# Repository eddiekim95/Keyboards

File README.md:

# Keyboards
Various keyboards designed through KiCad.

**Dualies_Split_Keyboard:**
- A split keyboard design featuring low profile switches and rotary encoders.

**Numpad:**
 - A 5x4 numpad KiCad project. Originally handwired.

**Split_Ortho:**
  - A standard split ortholinear. Used as a practice environment for learning KiCad.

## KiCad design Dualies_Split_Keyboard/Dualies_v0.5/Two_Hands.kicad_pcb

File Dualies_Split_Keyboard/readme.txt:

#Dualies_Split_Keyboard
A split keyboard with KiCad design and gerber files

**v0.5 -**

Initial version of a split ortholinear keyboard. Loosely modeled after the Sofle and the Lily58.
Designed around the Kailh Choc low profile switch.
Designed so each PCB can be flipped for each respective side.

Components:
  - [60] Kailh Choc low profile switches (30 for each side)
  - [62] 1N4148W Diodes (31x2)
  - [60] YS-SK6812MINI-E Addressable RGB LED (30x2)
  - [2] Pro Micro Microcontroller (1x2)
  - [2] SSD1306 OLED Display Module (1x2)
  - [2] EC11 Digital Encoder (1x2)
  - [2] TRRS Jack (1x2)
  - [2] 2.54mm pitch, 15.24mm chip socket (1x2)
  - [2] 3.5mm TRRS Cable (1x2)
 
**v1.0 -**

Optimized wire pathing and switch spacing. 
Better standoff placements. 
Added switch plate and bottom plate files.
Images of the files can be seen in the Pictures folder.

Components: 
  - (same as v0.5)

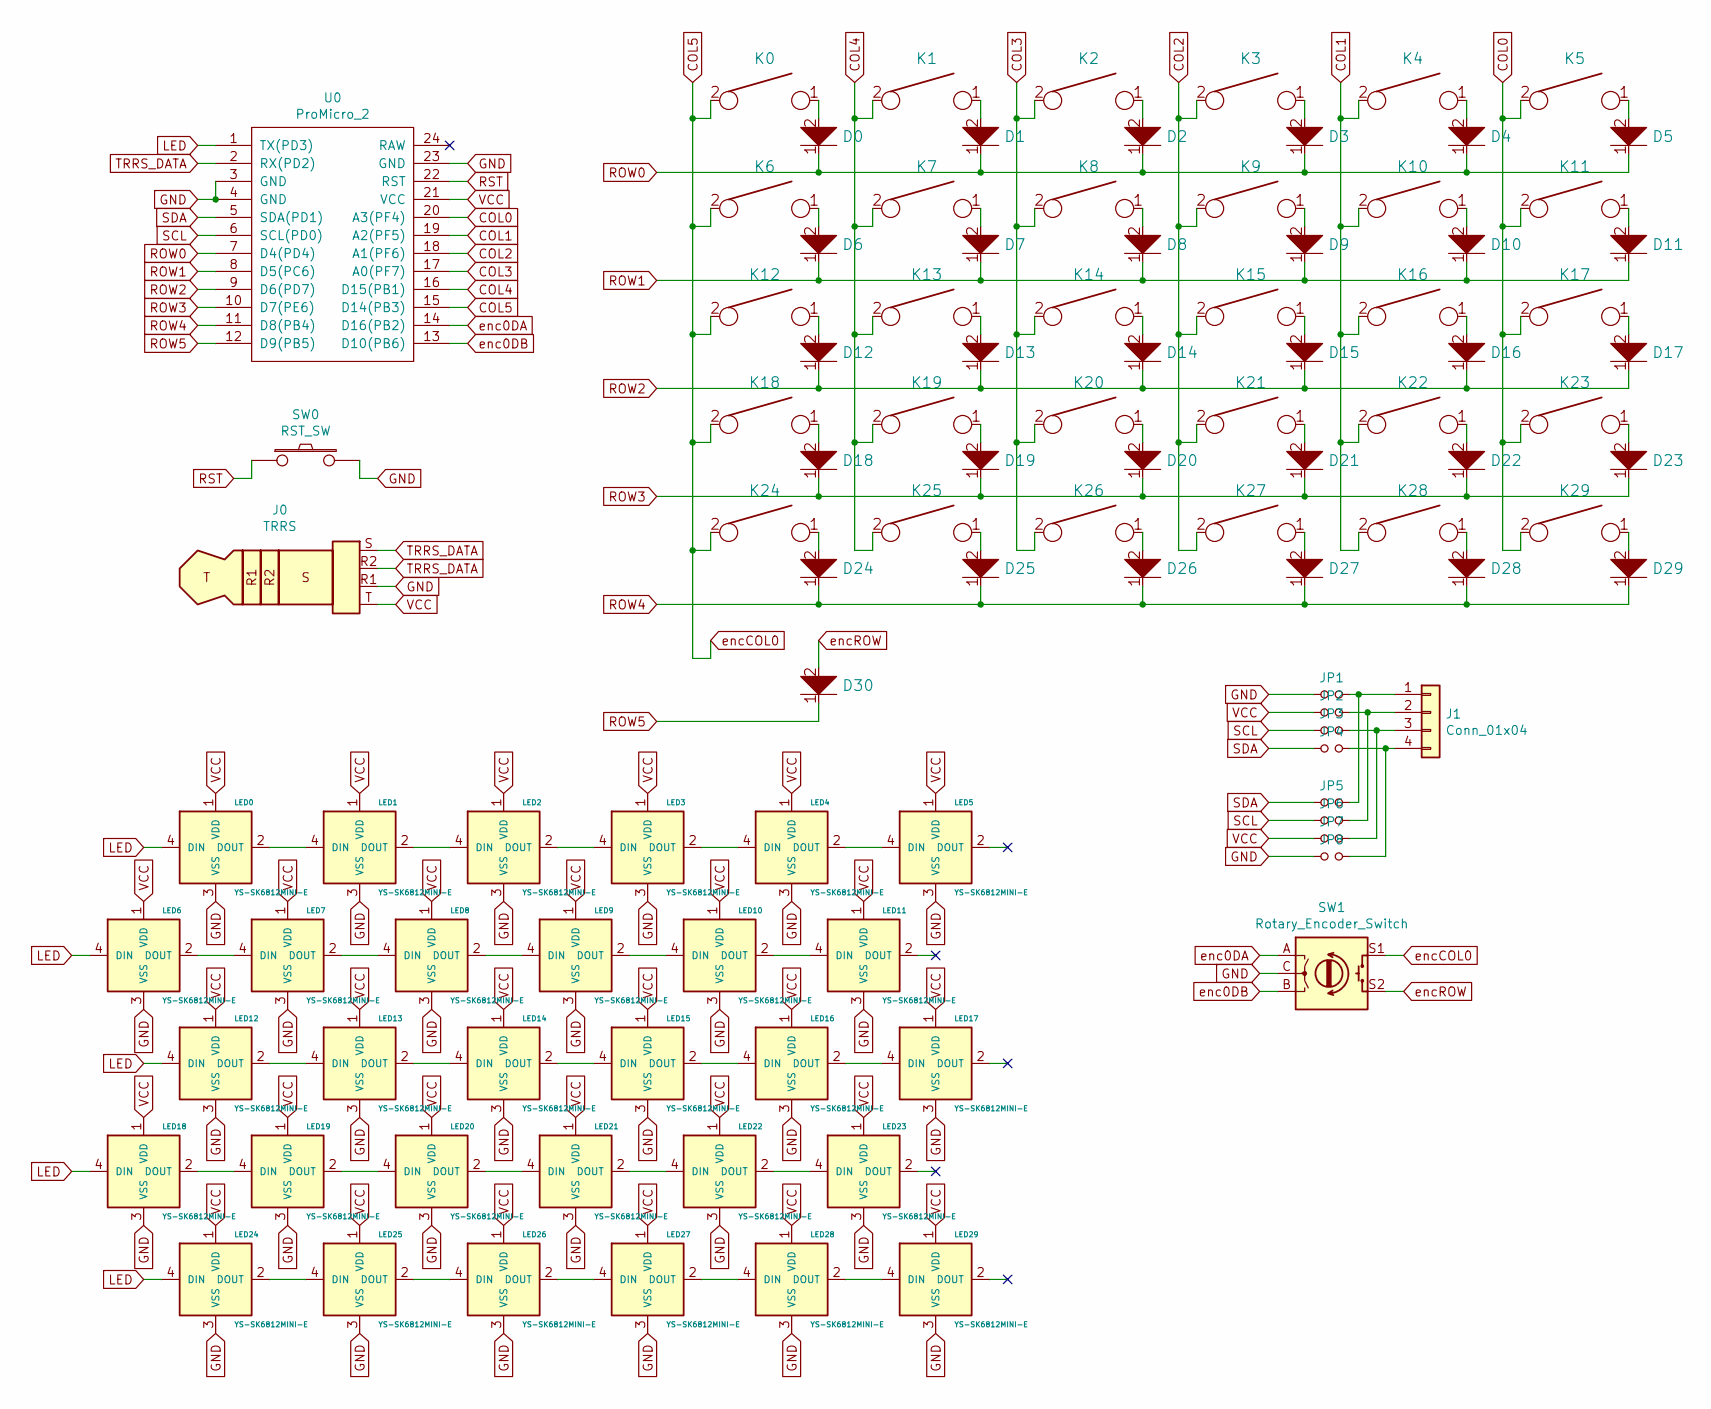
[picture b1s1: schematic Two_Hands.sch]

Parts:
D0, D1, D2, D3, D4, D5, D6, D7, D8, D9, D10, D11, D12, D13, D14, D15, D16, D17, D18, D19, D20, D21, D22, D23, D24, D25, D26, D27, D28, D29, D30: D; D_SOD123_axial_double
J0: TRRS; Jack_3.5mm_PJ320D_double
J1: Conn_01x04; PinHeader_1x04_P2.54mm_Vertical
JP1, JP2, JP3, JP4, JP5, JP6, JP7, JP8: Jumper_NO_Small; SolderJumper-2_P1.3mm_Open_Pad1.0x1.5mm
K0, K1, K2, K3, K4, K5, K6, K7, K8, K9, K10, K11, K12, K13, K14, K15, K16, K17, K18, K19, K20, K21, K22, K23, K24, K25, K26, K27, K28, K29: KEYSW; Kailh_Choc_100_Reversible
LED0, LED1, LED2, LED3, LED4, LED5, LED6, LED7, LED8, LED9, LED10, LED11, LED12, LED13, LED14, LED15, LED16, LED17, LED18, LED19, LED20, LED21, LED22, LED23, LED24, LED25, LED26, LED27, LED28, LED29: YS-SK6812MINI-E; YS-SK6812MINI-E_double
SW0: RST_SW; SW_PUSH_6mm
SW1: Rotary_Encoder_Switch; RotaryEncoder_Alps_EC12E-Switch_Vertical_H20mm
U0: ProMicro_2; ProMicro_double

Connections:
COL0: K5.2, K11.2, K17.2, K23.2, K29.2, U0.20 (A3(PF4))
COL1: K4.2, K10.2, K16.2, K22.2, K28.2, U0.19 (A2(PF5))
COL2: K3.2, K9.2, K15.2, K21.2, K27.2, U0.18 (A1(PF6))
COL3: K2.2, K8.2, K14.2, K20.2, K26.2, U0.17 (A0(PF7))
COL4: K1.2, K7.2, K13.2, K19.2, K25.2, U0.16 (D15(PB1))
COL5: K0.2, K6.2, K12.2, K18.2, K24.2, SW1.S1, U0.15 (D14(PB3)); also elsewhere on the board
GND: J0.R1, JP1.1, JP8.1, LED0.3 (VSS), LED1.3 (VSS), LED2.3 (VSS), LED3.3 (VSS), LED4.3 (VSS), LED5.3 (VSS), LED6.3 (VSS), LED7.3 (VSS), LED8.3 (VSS), LED9.3 (VSS), LED10.3 (VSS), LED11.3 (VSS), LED12.3 (VSS), LED13.3 (VSS), LED14.3 (VSS), LED15.3 (VSS), LED16.3 (VSS), LED17.3 (VSS), LED18.3 (VSS), LED19.3 (VSS), LED20.3 (VSS), LED21.3 (VSS), LED22.3 (VSS), LED23.3 (VSS), LED24.3 (VSS), LED25.3 (VSS), LED26.3 (VSS), LED27.3 (VSS), LED28.3 (VSS), LED29.3 (VSS), SW0.2, SW1.C, U0.3 (GND), U0.4 (GND), U0.23 (GND); also elsewhere on the board
LED: LED0.4 (DIN), LED6.4 (DIN), LED12.4 (DIN), LED18.4 (DIN), LED24.4 (DIN), U0.1 (TX(PD3))
unnamed: D0.2, K0.1
unnamed: D1.2, K1.1
unnamed: D2.2, K2.1
unnamed: D3.2, K3.1
unnamed: D4.2, K4.1
unnamed: D5.2, K5.1
unnamed: D6.2, K6.1
unnamed: D7.2, K7.1
unnamed: D8.2, K8.1
unnamed: D9.2, K9.1
unnamed: D10.2, K10.1
unnamed: D11.2, K11.1
unnamed: D12.2, K12.1
unnamed: D13.2, K13.1
unnamed: D14.2, K14.1
unnamed: D15.2, K15.1
unnamed: D16.2, K16.1
unnamed: D17.2, K17.1
unnamed: D18.2, K18.1
unnamed: D19.2, K19.1
unnamed: D20.2, K20.1
unnamed: D21.2, K21.1
unnamed: D22.2, K22.1
unnamed: D23.2, K23.1
unnamed: D24.2, K24.1
unnamed: D25.2, K25.1
unnamed: D26.2, K26.1
unnamed: D27.2, K27.1
unnamed: D28.2, K28.1
unnamed: D29.2, K29.1
unnamed: J1.1, JP1.2, JP5.2
unnamed: J1.2, JP2.2, JP6.2
unnamed: J1.3, JP3.2, JP7.2
unnamed: J1.4, JP4.2, JP8.2
unnamed: LED0.2 (DOUT), LED1.4 (DIN)
unnamed: LED1.2 (DOUT), LED2.4 (DIN)
unnamed: LED2.2 (DOUT), LED3.4 (DIN)
unnamed: LED3.2 (DOUT), LED4.4 (DIN)
unnamed: LED4.2 (DOUT), LED5.4 (DIN)
unnamed: LED6.2 (DOUT), LED7.4 (DIN)
unnamed: LED7.2 (DOUT), LED8.4 (DIN)
unnamed: LED8.2 (DOUT), LED9.4 (DIN)
unnamed: LED10.2 (DOUT), LED11.4 (DIN)
unnamed: LED9.2 (DOUT), LED10.4 (DIN)
unnamed: LED12.2 (DOUT), LED13.4 (DIN)
unnamed: LED13.2 (DOUT), LED14.4 (DIN)
unnamed: LED14.2 (DOUT), LED15.4 (DIN)
unnamed: LED15.2 (DOUT), LED16.4 (DIN)
unnamed: LED16.2 (DOUT), LED17.4 (DIN)
unnamed: LED18.2 (DOUT), LED19.4 (DIN)
unnamed: LED19.2 (DOUT), LED20.4 (DIN)
unnamed: LED20.2 (DOUT), LED21.4 (DIN)
unnamed: LED21.2 (DOUT), LED22.4 (DIN)
unnamed: LED22.2 (DOUT), LED23.4 (DIN)
unnamed: LED24.2 (DOUT), LED25.4 (DIN)
unnamed: LED25.2 (DOUT), LED26.4 (DIN)
unnamed: LED26.2 (DOUT), LED27.4 (DIN)
unnamed: LED27.2 (DOUT), LED28.4 (DIN)
unnamed: LED28.2 (DOUT), LED29.4 (DIN)
ROW0: D0.1, D1.1, D2.1, D3.1, D4.1, D5.1, U0.7 (D4(PD4))
ROW1: D6.1, D7.1, D8.1, D9.1, D10.1, D11.1, U0.8 (D5(PC6))
ROW2: D12.1, D13.1, D14.1, D15.1, D16.1, D17.1, U0.9 (D6(PD7))
ROW3: D18.1, D19.1, D20.1, D21.1, D22.1, D23.1, U0.10 (D7(PE6))
ROW4: D24.1, D25.1, D26.1, D27.1, D28.1, D29.1, U0.11 (D8(PB4))
ROW5: D30.1, U0.12 (D9(PB5))
RST: SW0.1, U0.22 (RST); also elsewhere on the board
SCL: JP3.1, JP6.1, U0.6 (SCL(PD0))
SDA: JP4.1, JP5.1, U0.5 (SDA(PD1))
TRRS_DATA: J0.R2, J0.S, U0.2 (RX(PD2))
VCC: J0.T, JP2.1, JP7.1, LED0.1 (VDD), LED1.1 (VDD), LED2.1 (VDD), LED3.1 (VDD), LED4.1 (VDD), LED5.1 (VDD), LED6.1 (VDD), LED7.1 (VDD), LED8.1 (VDD), LED9.1 (VDD), LED10.1 (VDD), LED11.1 (VDD), LED12.1 (VDD), LED13.1 (VDD), LED14.1 (VDD), LED15.1 (VDD), LED16.1 (VDD), LED17.1 (VDD), LED18.1 (VDD), LED19.1 (VDD), LED20.1 (VDD), LED21.1 (VDD), LED22.1 (VDD), LED23.1 (VDD), LED24.1 (VDD), LED25.1 (VDD), LED26.1 (VDD), LED27.1 (VDD), LED28.1 (VDD), LED29.1 (VDD), U0.21 (VCC)
enc0DA: SW1.A, U0.14 (D16(PB2)); also elsewhere on the board
enc0DB: SW1.B, U0.13 (D10(PB6)); also elsewhere on the board
encROW: D30.2, SW1.S2; also elsewhere on the board

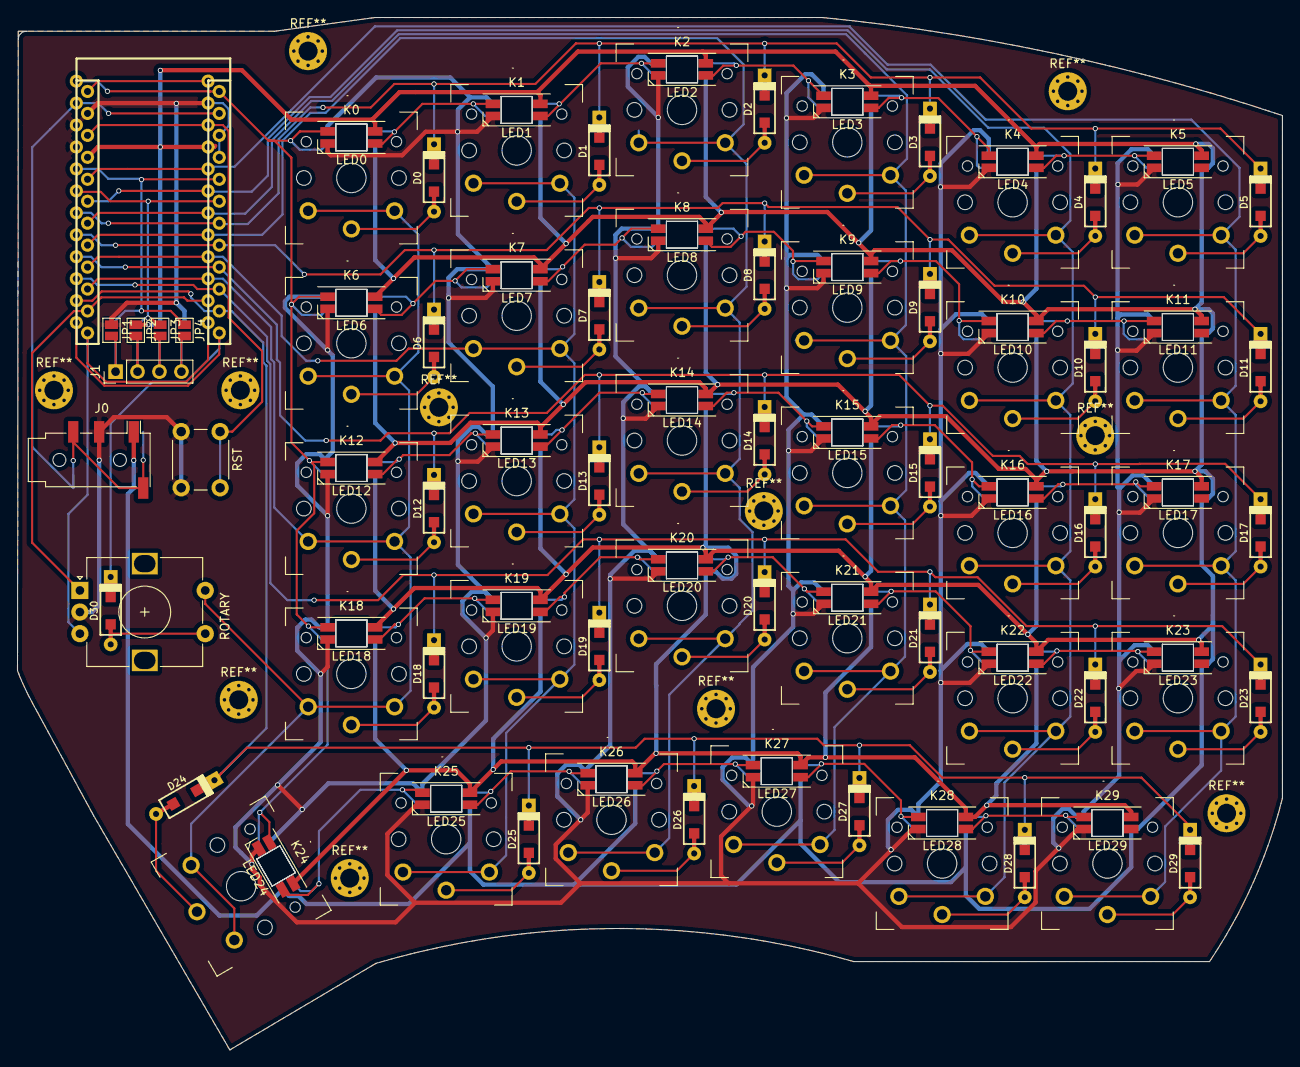
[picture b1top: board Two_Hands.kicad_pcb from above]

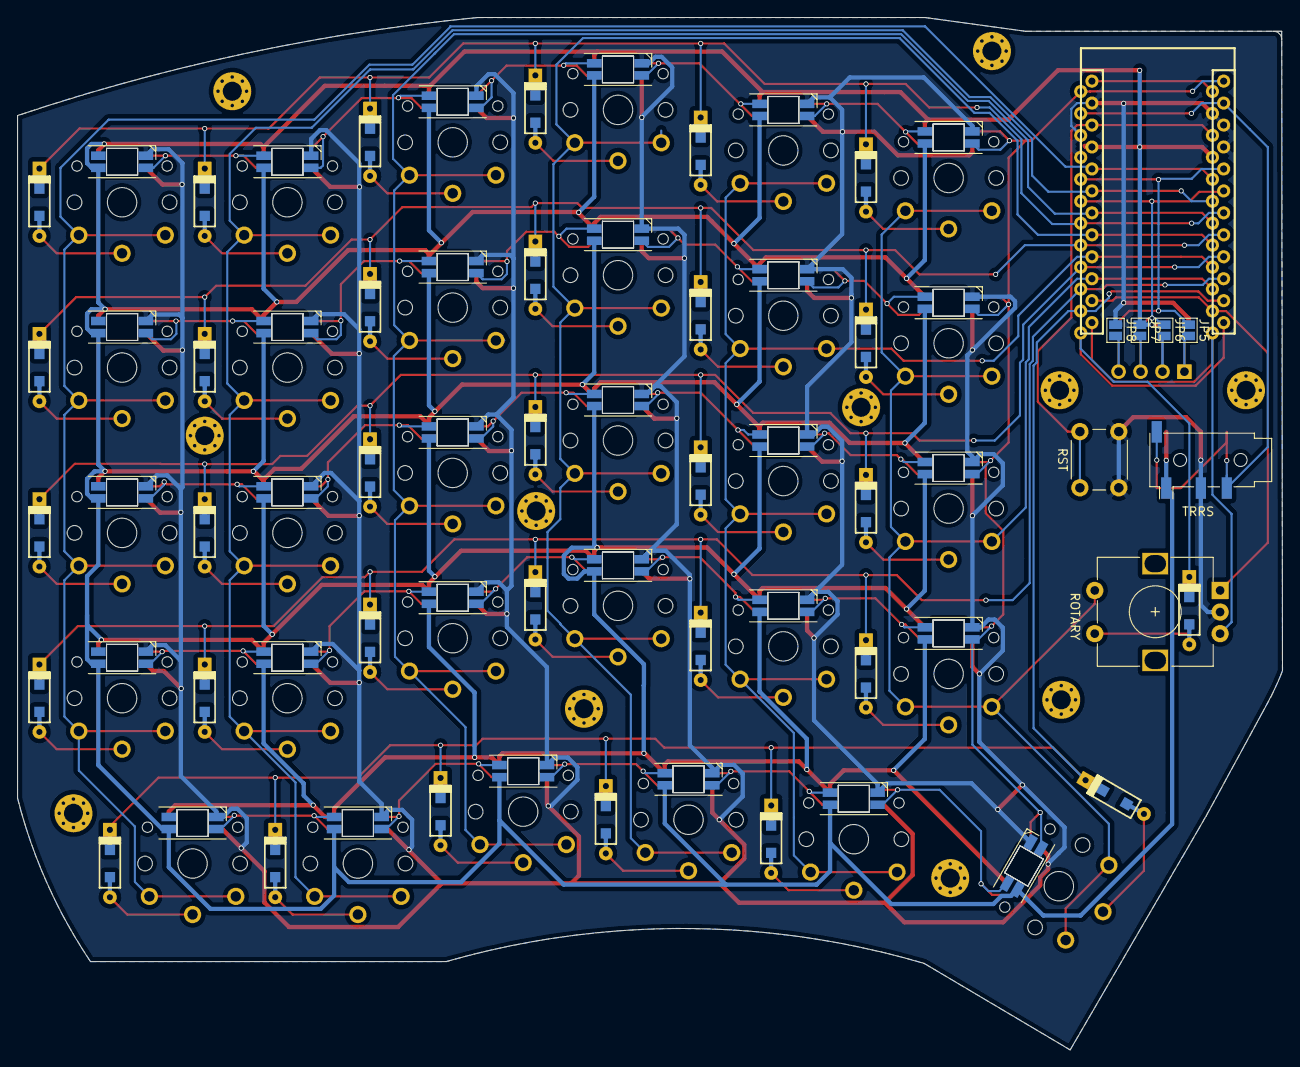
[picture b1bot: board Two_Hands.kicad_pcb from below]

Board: 2 copper layers, 146.3 x 119.4 mm, 106 parts (6 on the bottom side), 81 nets.

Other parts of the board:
ROTARY: Rotary_Encoder_Switch; RotaryEncoder_Alps_EC12E-Switch_Vertical_H20mm
ROTARY#2: Rotary_Encoder_Switch; RotaryEncoder_Alps_EC12E-Switch_Vertical_H20mm
RST: RST_SW; SW_PUSH_6mm
RST#2: RST_SW; SW_PUSH_6mm

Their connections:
COL5: ROTARY#2.S1; also elsewhere on the board
GND: ROTARY#2.C, RST#2.2; also elsewhere on the board
RST: RST#2.1; also elsewhere on the board
enc0DA: ROTARY#2.A; also elsewhere on the board
enc0DB: ROTARY#2.B; also elsewhere on the board
encROW: ROTARY#2.S2; also elsewhere on the board

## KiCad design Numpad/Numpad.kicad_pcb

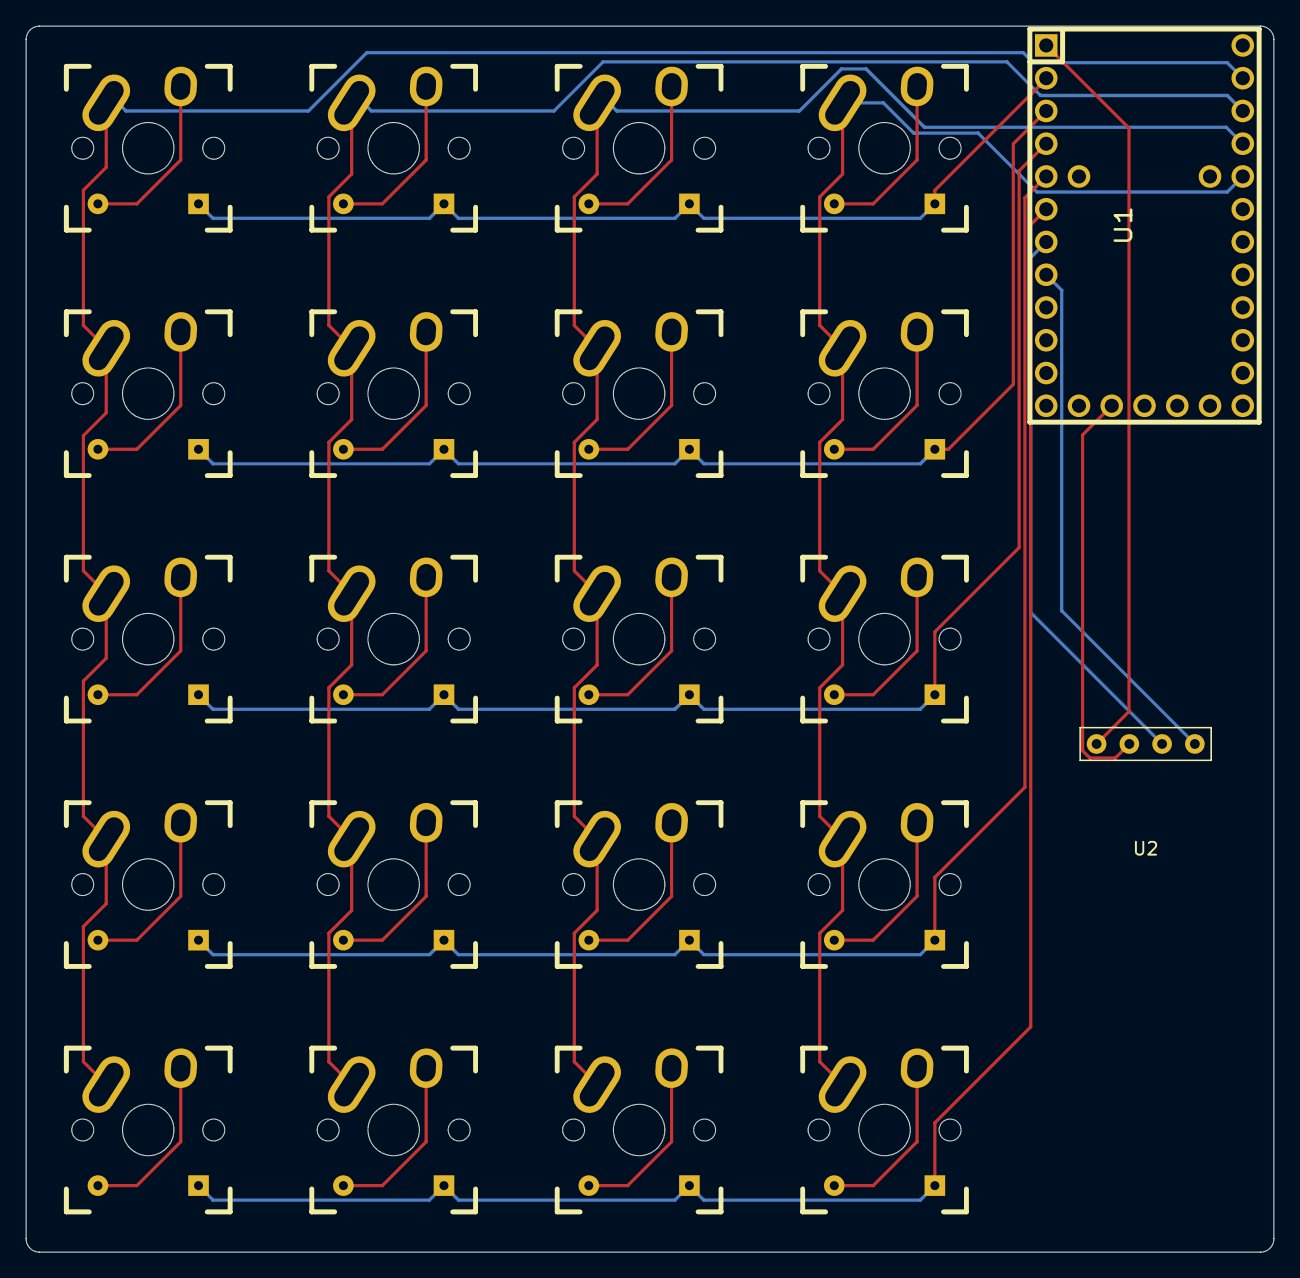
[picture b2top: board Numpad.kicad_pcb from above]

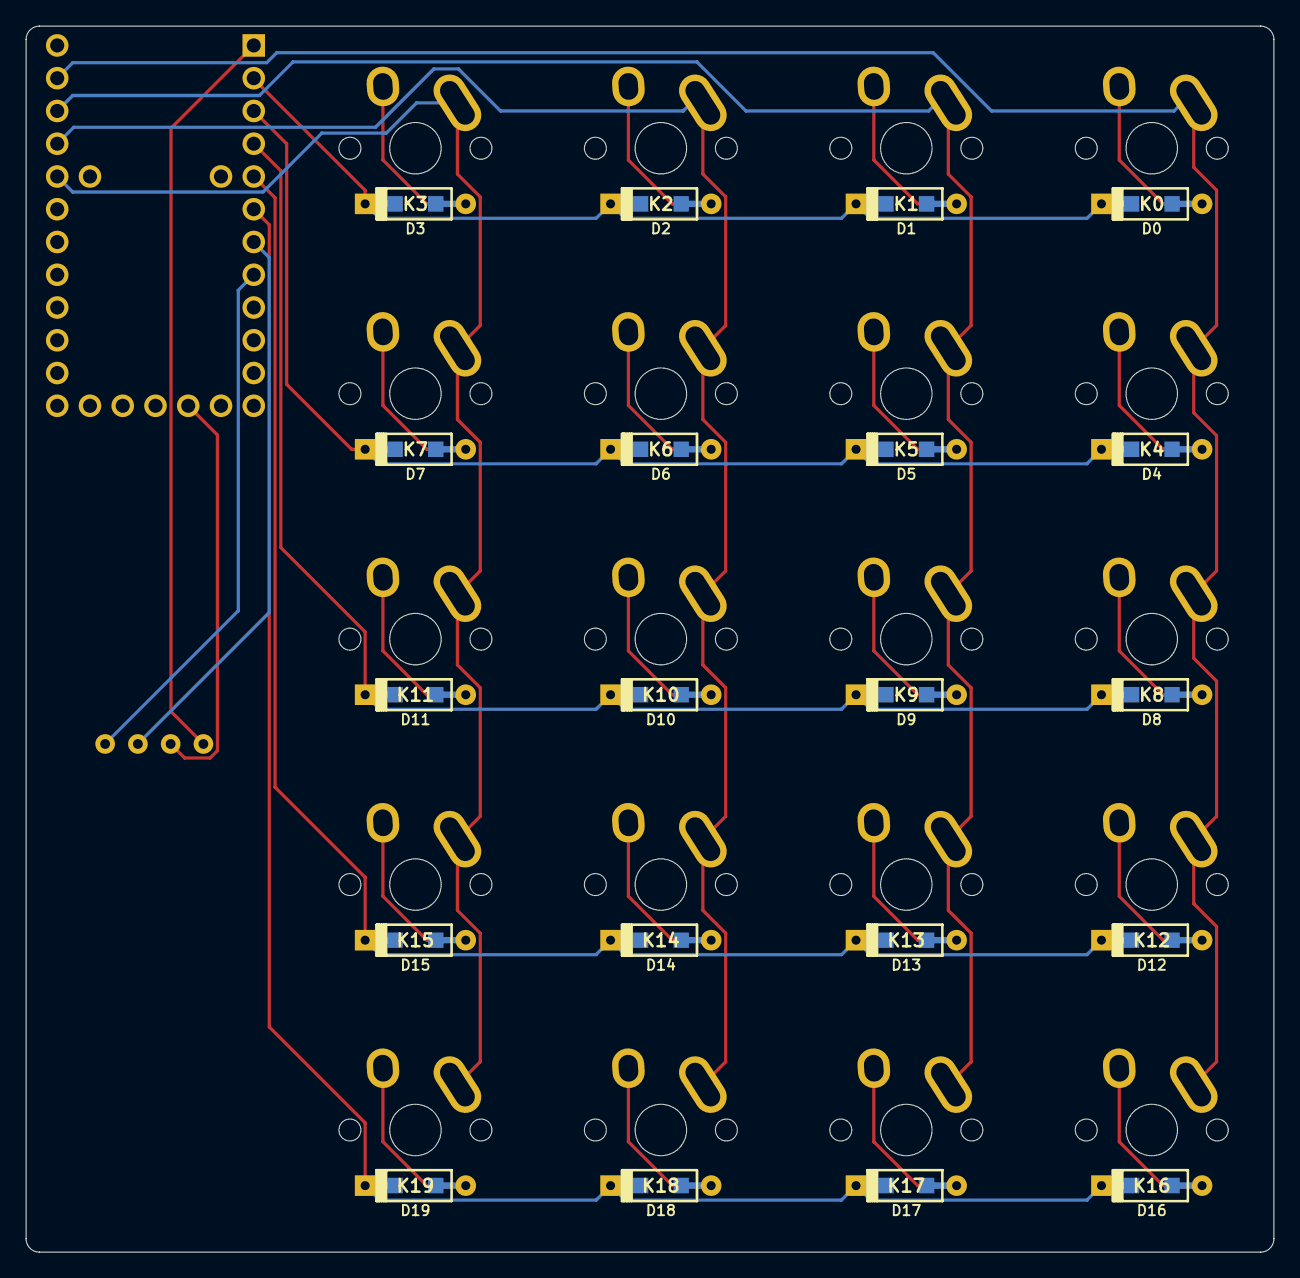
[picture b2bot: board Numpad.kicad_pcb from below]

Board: 2 copper layers, 96.8 x 95.1 mm, 42 parts (20 on the bottom side), 33 nets.

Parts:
D0, D1, D2, D3, D4, D5, D6, D7, D8, D9, D10, D11, D12, D13, D14, D15, D16, D17, D18, D19: D; D_SOD123_axial
K0, K1, K2, K3, K4, K5, K6, K7, K8, K9, K10, K11, K12, K13, K14, K15, K16, K17, K18, K19: KEYSW; Mx_Alps_100
U1: TEENSY2.0; Teensy_20
U2: 0.91'_OLED

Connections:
unnamed: D0.1, D1.1, D2.1, D3.1, U1.2
unnamed: D0.2, K0.2
unnamed: D1.2, K1.2
unnamed: D2.2, K2.2
unnamed: D3.2, K3.2
unnamed: D4.1, D5.1, D6.1, D7.1, U1.3
unnamed: D4.2, K4.2
unnamed: D5.2, K5.2
unnamed: D6.2, K6.2
unnamed: D7.2, K7.2
unnamed: D8.2, K8.2
unnamed: D9.2, K9.2
unnamed: D8.1, D9.1, D10.1, D11.1, U1.4
unnamed: D10.2, K10.2
unnamed: D11.2, K11.2
unnamed: D12.1, D13.1, D14.1, D15.1, U1.5
unnamed: D12.2, K12.2
unnamed: D13.2, K13.2
unnamed: D14.2, K14.2
unnamed: D15.2, K15.2
unnamed: D16.1, D17.1, D18.1, D19.1, U1.6
unnamed: D16.2, K16.2
unnamed: D17.2, K17.2
unnamed: D18.2, K18.2
unnamed: D19.2, K19.2
unnamed: K0.1, K4.1, K8.1, K12.1, K16.1, U1.28
unnamed: K1.1, K5.1, K9.1, K13.1, K17.1, U1.27
unnamed: K2.1, K6.1, K10.1, K14.1, K18.1, U1.26
unnamed: K3.1, K7.1, K11.1, K15.1, K19.1, U1.25
unnamed: U1.1, U2.1
unnamed: U1.7, U2.3
unnamed: U1.8, U2.4
unnamed: U1.14, U2.2

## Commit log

2021-03-17 Rename readme.txt to README.MD
